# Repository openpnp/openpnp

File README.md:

# OpenPnP

Open Source SMT Pick and Place Hardware and Software

## Introduction

OpenPnP is a project to create the plans, prototype and software for a completely Open Source SMT
pick and place machine that anyone can afford. I believe that with the ubiquity of cheap, precise
motion control hardware, some ingenuity and plenty of Open Source software it should be possible
to build and own a fully functional SMT pick and place machine for under $1000.

## Project Status

OpenPnP is stable and in wide use. It is still under heavy development and new features are added continuously. See the [Downloads](http://openpnp.org/downloads) page to get started.

If you would like to keep up with our progress you can
[Watch this project on GitHub](http://github.com/openpnp/openpnp), check out
[our Twitter](http://twitter.com/openpnp), [join the discussion group](http://groups.google.com/group/openpnp),
or come chat with us on [Discord](https://discord.gg/EmsrFVx).

## Contributing

Before starting work on a pull request, please read: https://github.com/openpnp/openpnp/wiki/Developers-Guide#contributing

Summary of guidelines:

* One pull request per issue.
* Describe the change.
* Follow the coding style.
* Include tests and documentation.
* Think of the big picture.

## Thanks

Many thanks to ej-technologies for providing a complimentary license of install4j. install4j
creates high quality, professional installers for Java applications.

More information at http://www.ej-technologies.com/products/install4j/overview.html.

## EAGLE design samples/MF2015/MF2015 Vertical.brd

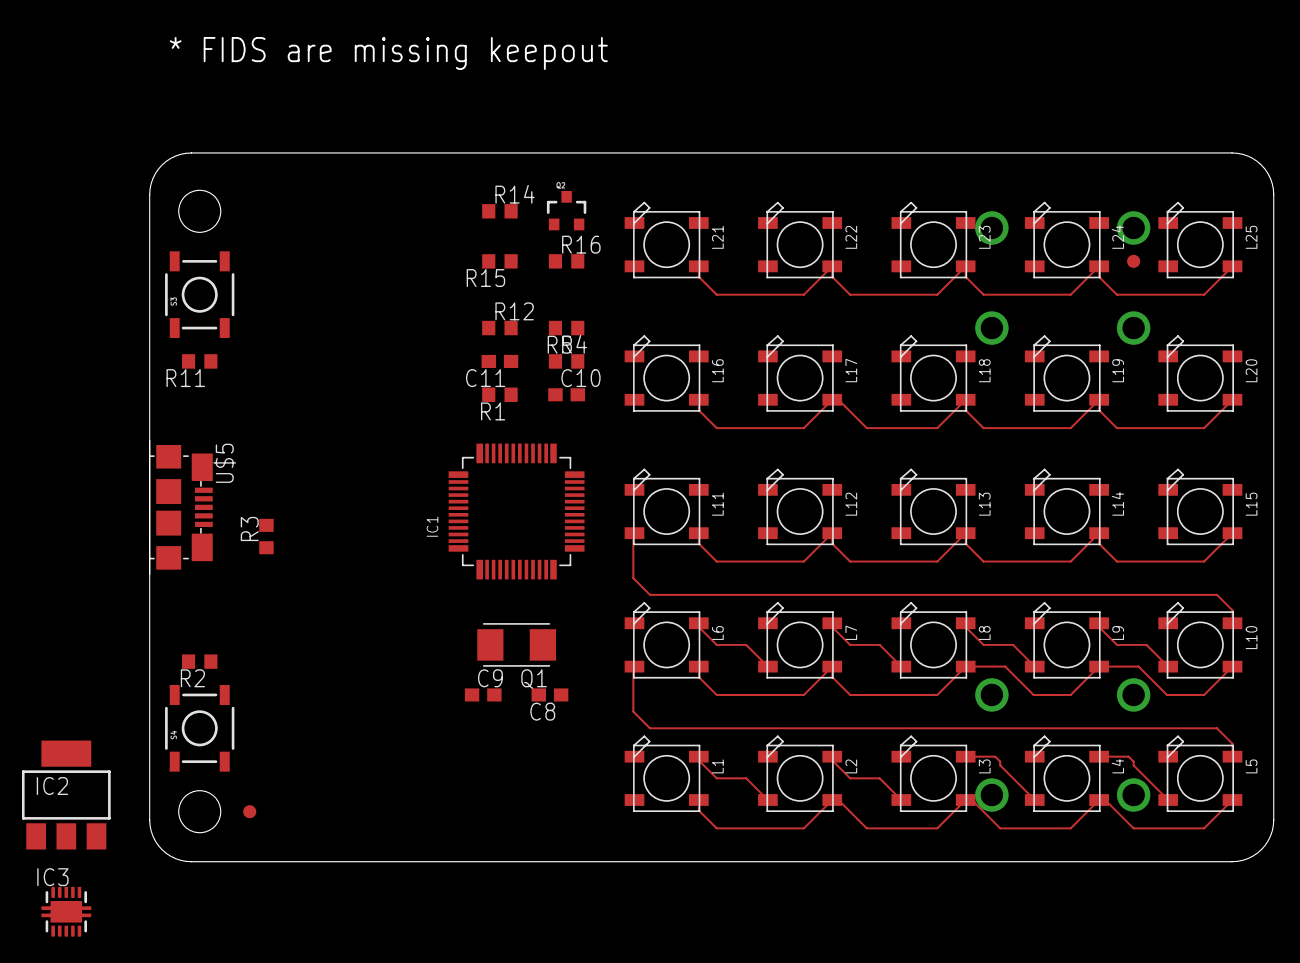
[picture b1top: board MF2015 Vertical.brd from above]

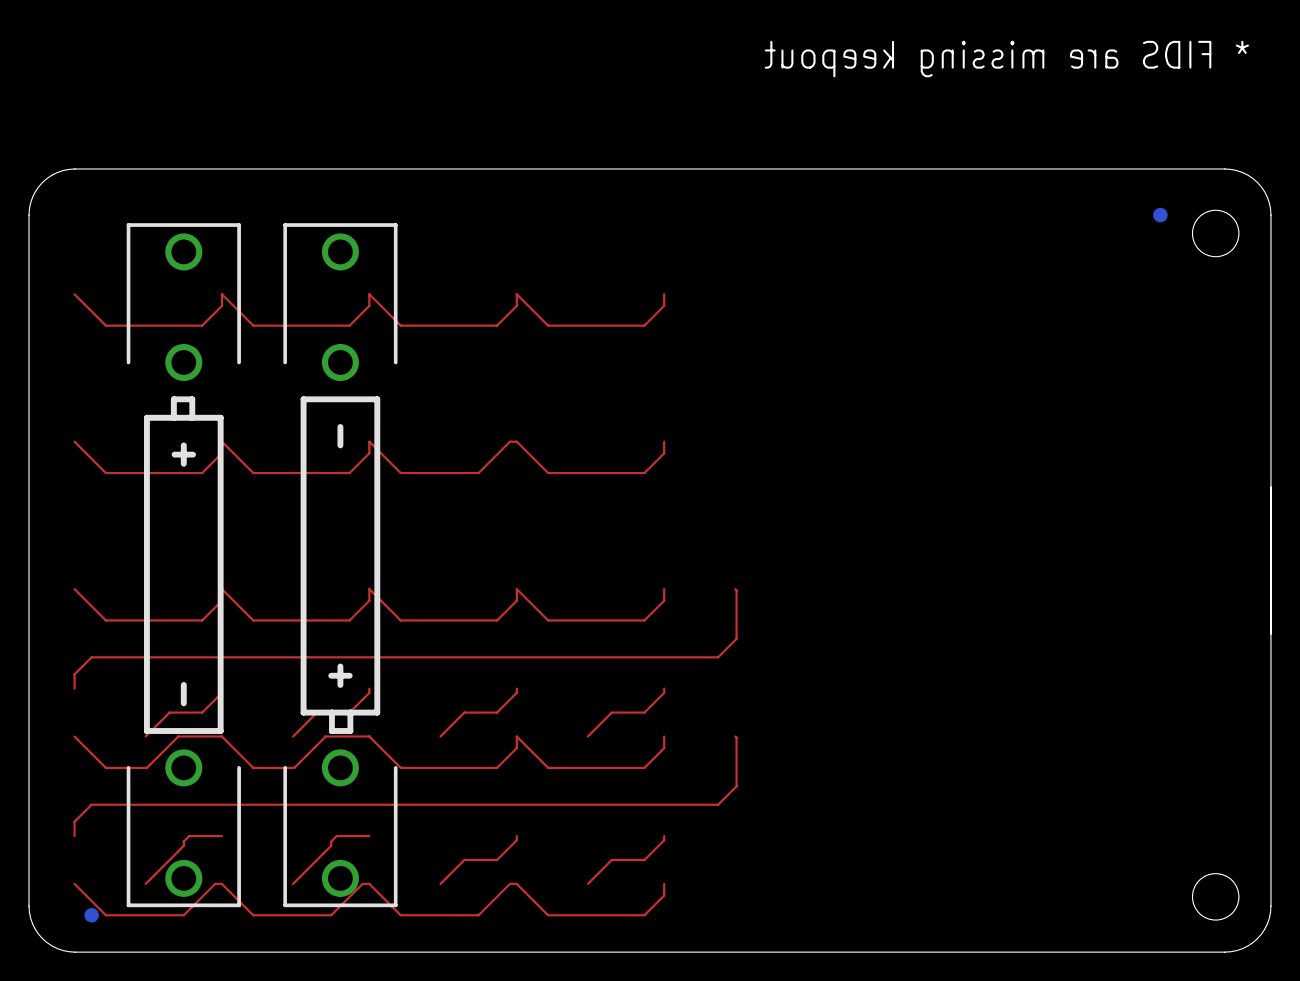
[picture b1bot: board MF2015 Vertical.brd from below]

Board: 2 copper layers, 85.6 x 54.0 mm, 53 parts (4 on the bottom side), 44 nets.

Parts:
BAT1, BAT2: BATTERY-AAA-KIT
C8, C9, C10, C11: 18pF; C0603
FID1, FID2, FID3, FID4: FIDUCIAL1X2; FIDUCIAL-1X2
IC1: LPC11U24FBD48/401; LQFP48
IC2: LD117AS12TR; SOT223
IC3: TPS61200; S-PDSO-N10
L1, L2, L3, L4, L5, L6, L7, L8, L9, L10, L11, L12, L13, L14, L15, L16, L17, L18, L19, L20, L21, L22, L23, L24, L25: WS2812B
Q1: CRYSTAL-SMD-5X3.2-2PIN
Q2: BC857B; SOT23-3
R1, R4: 33; R0603
R2, R5, R11: 10K; R0603
R3: 1M; R0603
R12: 100; R0603
R14: 1.5K; R0603
R15: 3K; R0603
R16: 24K; R0603
S3: Reset; TACTILE_SWITCH_SMD
S4: ISP; TACTILE_SWITCH_SMD
U$5: USB-MICROB-SMDRECEPT; USB-MICROB-RECEPT

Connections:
GND: BAT2.GND@1, C8.2, C9.2, C10.2, C11.2, IC1.5, IC1.41, IC3.9, L1.3-GND, L2.3-GND, L3.3-GND, L4.3-GND, L5.3-GND, L6.3-GND, L7.3-GND, L8.3-GND, L9.3-GND, L10.3-GND, L11.3-GND, L12.3-GND, L13.3-GND, L14.3-GND, L15.3-GND, L16.3-GND, L17.3-GND, L18.3-GND, L19.3-GND, L20.3-GND, L21.3-GND, L22.3-GND, L23.3-GND, L24.3-GND, L25.3-GND, R3.1, R5.1, S3.1, S3.2, S4.1, S4.2, U$5.5
unnamed: L1.2-DOUT, L2.4-DIN
unnamed: L2.2-DOUT, L3.4-DIN
unnamed: L3.2-DOUT, L4.4-DIN
unnamed: L4.2-DOUT, L5.4-DIN
unnamed: L5.2-DOUT, L6.4-DIN
unnamed: L6.2-DOUT, L7.4-DIN
unnamed: L7.2-DOUT, L8.4-DIN
unnamed: L8.2-DOUT, L9.4-DIN
unnamed: L9.2-DOUT, L10.4-DIN
unnamed: L10.2-DOUT, L11.4-DIN
unnamed: L11.2-DOUT, L12.4-DIN
unnamed: L12.2-DOUT, L13.4-DIN
unnamed: L13.2-DOUT, L14.4-DIN
unnamed: L14.2-DOUT, L15.4-DIN
unnamed: L15.2-DOUT, L16.4-DIN
unnamed: L16.2-DOUT, L17.4-DIN
unnamed: L17.2-DOUT, L18.4-DIN
unnamed: L18.2-DOUT, L19.4-DIN
unnamed: L19.2-DOUT, L20.4-DIN
unnamed: L20.2-DOUT, L25.2-DOUT
unnamed: L24.2-DOUT, L25.4-DIN
unnamed: L23.2-DOUT, L24.4-DIN
unnamed: L22.2-DOUT, L23.4-DIN
unnamed: L21.2-DOUT, L22.4-DIN
unnamed: C9.1, IC1.6, Q1.P$2
unnamed: C8.1, IC1.7, Q1.P$1
unnamed: C10.1, R1.1, R14.1, U$5.3
unnamed: IC1.4, R2.1, S4.3, S4.4
unnamed: IC1.20, R1.2
unnamed: IC1.3, R11.1, S3.3, S3.4
unnamed: IC1.19, R4.2
unnamed: C11.1, R4.1, U$5.2
unnamed: R12.1, U$5.1
unnamed: R3.2, U$5.4
unnamed: Q2.1, R15.1, R16.1
unnamed: Q2.3, R14.2
unnamed: BAT1.GND@1, BAT2.PWR@1
unnamed: IC1.25, L1.4-DIN
unnamed: L1.1-VDD, L2.1-VDD, L3.1-VDD, L4.1-VDD, L5.1-VDD, L6.1-VDD, L7.1-VDD, L8.1-VDD, L9.1-VDD, L10.1-VDD, L11.1-VDD, L12.1-VDD, L13.1-VDD, L14.1-VDD, L15.1-VDD, L16.1-VDD, L17.1-VDD, L18.1-VDD, L19.1-VDD, L20.1-VDD, L21.1-VDD, L22.1-VDD, L23.1-VDD, L24.1-VDD, L25.1-VDD
PP: IC3.PP, IC3.PP@1, IC3.PP@2
USB_CONNECT: IC1.22, R15.2
USB_VBUS: IC1.14, R5.2, R12.2
VCC: Q2.2, R2.2, R11.2, R16.2

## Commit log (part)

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2025-03-17 Draw the visual feedback circles in the fiducial pipeline
2025-03-18 Add scriptState, a public Map attribute of the configuration object, which can be used by scripts as a namespace for storing arbitrary state.
2025-03-21 more changes
2025-03-21 Fix feed options after real machine test
2025-03-21 Moved FeederWithOptions stuff to ReferenceFeeder
2025-03-21 Lastest javadoc on successful build 1592 auto-pushed to gh-pages
2025-03-23 Lastest javadoc on successful build 1595 auto-pushed to gh-pages
2025-03-24 Provide the pipeline with the essential 'camera' property
2025-03-27 implement FeedOptions for PushPullFeeder
2025-03-27 An empty delay command should be treated the same as a missing delay command
2025-03-29 Lastest javadoc on successful build 1606 auto-pushed to gh-pages
2025-04-05 Portability enum type added to provide more options and a better readability uniqueness changes to a uuid that is stored in a file named machine.uuid
2025-04-08 Converted several JPanels to wizards and cleaned up bindings when the wizards are removed
    Also changed the names of the new wizards to end with Wizard and moved to proper packages
2025-04-10 - Location.convertToUnits() enhanced to return this in case units does not change - TravelLocation changed to extend Location
2025-04-12 add a unit test to confirm that the properties file is in normal form
2025-04-12 Lastest javadoc on successful build 1615 auto-pushed to gh-pages
2025-04-14 Convert different OS line endings to LFs before doing the comparison
2025-04-15 Lastest javadoc on successful build 1621 auto-pushed to gh-pages
2025-04-16 Lastest javadoc on successful build 1623 auto-pushed to gh-pages
2025-04-29 calculate travel time using backlash calibration data
2025-05-06 added
2025-05-07 A couple of revision suggestions
    1.BoardPlacementsPanel：Fix the missing Default setting option in errorHandling.
    2.JobPlacementsPanel：Set multi-language translation for Placement.Type.Fiducial&Placement.
    3.PlacementsHolderPlacementsTableModel：Extract the column name of “Placed” and “Status” as keys for multi-language translation.
    4.PackageVisionWizard：Add the missing key for “% Roundness”.
    5.ReferenceStripFeederConfigurationWizard：①Extract the ToolTipText for RotationInTapeLabel.②Increase the width of the JTextField for RotationInTape to display the entire numerical value. ③Put the Too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
    6.Fiduc
2025-05-09 actuate methods that do not rely on overloading, for the benefit of scripting languages where it might not be so easy to hit the right overloaded method
2025-05-13 Lastest javadoc on successful build 1641 auto-pushed to gh-pages
2025-05-16 nozzle order
2025-05-16 Fix the TSM test 'temperature' loop termination condition. Extend the test by running it multiple times with machines of different acceleration profiles. The route is validated by calculating the act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
2025-05-17 fix AllowUucoordinatedLabel
    AllowUuncoordinatedLabel is wrong，there is an extra letter 'u'.
2025-05-17 Continue to correct the errors
    1.fix <body style=\"text-align:right\"> to <body style\="text-align\:right">
    2. fix <span style=\"color:#FF0000\"> to <span style\="color\:\#FF0000">
2025-05-17 Try again to use GCodeAsyncDriver.AdvancedSettingsWizard.title
    Follow the Java Maven message :
    "The first error was found on this line:
    GcodeAsyncDriver.AdvancedSettingsWizard.title=Advanced Settings
    But was expected to be:
    GCodeDriver.Console.title=Console"
    Change Gcode… to GCode…
2025-05-20 Lastest javadoc on successful build 1654 auto-pushed to gh-pages
2025-05-23 - endTemperatur parameter explained and changed to startTemperatur/1000 - test extended to apply individual tight upper and lower limits.
2025-05-23 Lastest javadoc on successful build 1662 auto-pushed to gh-pages
2025-05-26 kicad pcbnew importer
2025-05-28 change ReferenceStripFeeder to do sprocket hole detection using a more modern pipeline using DetectCircularSymmetry, equivalent to the pipeline used in PushPullFeeder.
2025-05-31 Add Rank feature
2025-06-02 a constant for the default rank value
2025-06-02 we need to respect rank in planWithNozzleTipChange, therefore we can do the sort very much earlier
2025-06-04 Ensure the wizard container is set
2025-06-05 Lastest javadoc on successful build 1690 auto-pushed to gh-pages
2025-06-10 tidy up some test logic
2025-06-11 add changelog item
2025-06-11 gcodeasyncdriver: bubble up errors through machine coordination
    Previous to this patch, a timeout during M400 would softlock openpnp.
    Fixes #1848
2025-06-15 Fixed forgotten escape character for regex.
2025-06-19 added svg report to job planner unit test
2025-06-19 A new feeder strategy to avoid having two nozzles picking from same feeder. This will eventually be useful with photon feeders (but other changes are needed first)
2025-06-19 A cosmetic improvement to the svg jobplanner report. These are actually useful now; I should share some on github PR
2025-06-19 A better system for setting TSM start location. The goal is to keep the route stable between cycles when the input data is changing slightly
2025-06-19 LICENSE-AGREEMENT
2025-06-23 Lastest javadoc on successful build 1721 auto-pushed to gh-pages
2025-07-01 move the test panels off z=0 to make it physically realistic
2025-07-07 Added prelimenary grbl controller settings to openpnp gui.
2025-07-08 remove unused variable
2025-07-11 Add 7 missing keys in the CameraVisionConfigurationWizard.java
    The Value are already in the translations.properties file.
    Just missing the keys in the CameraVisionConfigurationWizard.java
2025-07-11 Make the key for "General" of the Border.title in the JobProcessorGeneralPanel
    Make the key for "General" of the Border.title in the JobProcessorGeneralPanel
2025-07-22 Update the Chinese UI translation for OpenPnP
    More than 2 years have passed since the first PR #1523.
    This time it is a recreated translations_zh_CN document.
    Keep up with OpenPnP.
2025-07-29 refactor: улучшено форматирование кода и добавлены комментарии для headless режима
2025-07-29 Version number; change to 2.5
2025-07-31 Lastest javadoc on successful build 1750 auto-pushed to gh-pages
2025-08-06 fix "Using estimated travl cost" logging to "Using estimated travel cost as metric"
2025-08-07 Lastest javadoc on successful build 1759 auto-pushed to gh-pages
2025-08-16 Some extra logging for the cases where a JobPlanner Locator class returns a null Location in place of an exception
2025-08-19 remove redundant method
2025-08-20 Lastest javadoc on successful build 1766 auto-pushed to gh-pages
2025-08-20 Lastest javadoc on successful build 1768 auto-pushed to gh-pages
2025-08-26 add the Job.Error script
2025-08-29 GUI tidy up. Remove the Tape Type field from strip feeder, because it is unused. Add a tooltip to the Tape Specification field, because it is hardly used.
2025-09-02 Lastest javadoc on successful build 1776 auto-pushed to gh-pages
2025-09-02 Lastest javadoc on successful build 1780 auto-pushed to gh-pages
2025-09-05 Previously script events were run if the filename matches 'EventName.ext'. With this change we also run 'EventName.YourTextInHere.ext'.
2025-09-05 test that this script is not run
2025-09-08 Lastest javadoc on successful build 1785 auto-pushed to gh-pages
2025-09-11 Lastest javadoc on successful build 1789 auto-pushed to gh-pages
2025-09-18 a new findFeeder method which is aware of travel distance
2025-09-18 feeders keep track of whether the parts they supply cause any faults, and feeders will be disabled if there are too many. the number of recent faults is shown on the panel
2025-09-18 each placement can be retried multiple times
2025-09-30 fix the longer-than-typical dwell time on the last placement of a job
2025-09-30 Lastest javadoc on successful build 1799 auto-pushed to gh-pages
2025-10-02 Lastest javadoc on successful build 1802 auto-pushed to gh-pages
2025-10-11 Lastest javadoc on successful build 1804 auto-pushed to gh-pages
2025-10-22 avoid drawing a mask circle of zero radius, or a mask rectangle of zero width or height. Such masks are used to wipe the whole image, but they can sometimes leave a stray pixel
2025-11-01 photonfeeder: add a button to feed 1mm
    This helps a lot when fine tweaking the position of components after loading a reel.
    The physical buttons on the feeder advance by 2mm which is too much for 2mm pitch parts.
2025-11-07 a new mechanism to defer turning off any camera lights until the end of a batch of capture operations
2025-11-11 multiple bottomvision cameras
2025-11-12 missing gui and feature integration added
2025-12-06 Strip GUI tests
2025-12-08 thread safety
2025-12-08 Lastest javadoc on successful build 1822 auto-pushed to gh-pages
2025-12-08 Lastest javadoc on successful build 1825 auto-pushed to gh-pages
2025-12-10 Lastest javadoc on successful build 1827 auto-pushed to gh-pages
2025-12-15 feat: Add Board Scanner dialog for scanning, stitching, and saving board images.
2025-12-15 feat: Move board scanning to the board context menu in job. fix: apply rotation to board image capture path planning.
2025-12-16 Fix: Preview Placements Overlay Issue for boards without set dimensions Fix: Lighting in Board Scanner and Feeder Image Dialogs
2025-12-16 prevent divide by zero and other problems by ensuring that the number of rows and columns is never less than 1
2025-12-17 photonfeeder: change the naming scheme in-order to order by slot
    Ordering by name now orders by physical slots;
    which is way more useful than by UUIDs.
2025-12-17 fix: use the placement extents by default to calculate the scan area. Apparently some boards have the origin off in space.
2025-12-18 Lastest javadoc on successful build 1840 auto-pushed to gh-pages
2025-12-18 implement a delay
2025-12-18 Lastest javadoc on successful build 1845 auto-pushed to gh-pages
2025-12-19 Lastest javadoc on successful build 1847 auto-pushed to gh-pages
2026-01-03 Add parallax based depth measurement as an autofocus provider.
    ---
    How to Set Up and Use Parallax Z-Height Estimation
    This feature estimates the Z-height of parts or PCBs using parallax from a single down-looking perspective camera by moving the head in X/Y.
    Prerequisites
    Camera Type: Must be a Perspective camera (telecentric lenses will not work).
    Movement: The camera must be capable of moving in X and Y. Z movement is not required for calibration as it relies on objects of different heights.
2026-01-05 Replace `Thread.sleep()`+`capture()` with `settleAndCapture()`
2026-01-09 Lastest javadoc on successful build 1853 auto-pushed to gh-pages
2026-01-24 improve CHANGES wording following review
2026-02-08 Use advanced camera calibration to populate the 3D Calibration data.
2026-03-01 Lastest javadoc on successful build 1867 auto-pushed to gh-pages
2026-03-20 I truly missed Joystic support so I added linux based gamepad support for Thrustmaster GP XID. Now the left joystic steers X and Y the right joystic steers Z and C axis. The fire buttons and left-rig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
2026-03-25 Option added to Suppress Dynamic Compensation during tip unloads
2026-04-11 Add macOS camera entitlement for hardened runtime
    The notarized macOS build uses hardened runtime, which blocks camera
    access without an explicit com.apple.security.device.camera entitlement.
    The existing NSCameraUsageDescription in Info.plist only provides the
    permission dialog text but does not grant the entitlement itself.
2026-04-17 Add HWGC SMT550 driver
    Full OpenPnP driver for the HWGC SMT550 pick-and-place machine using
    the Exar XR21V1410 USB-UART bridge at 460800 baud.
    Features:
    - Motion control: XY gantry, 4 nozzles with shared Z motor pairs
    (N1+N2, N3+N4), 4 rotation axes
    - Coordinate system: Y-axis inversion (machine Y=0 at top-left,

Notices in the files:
parts and their libraries:
SparkFun-DiscreteSemi: Licensing: CC v3.0 Share-Alike You are welcome to use this library for commercial purposes.
